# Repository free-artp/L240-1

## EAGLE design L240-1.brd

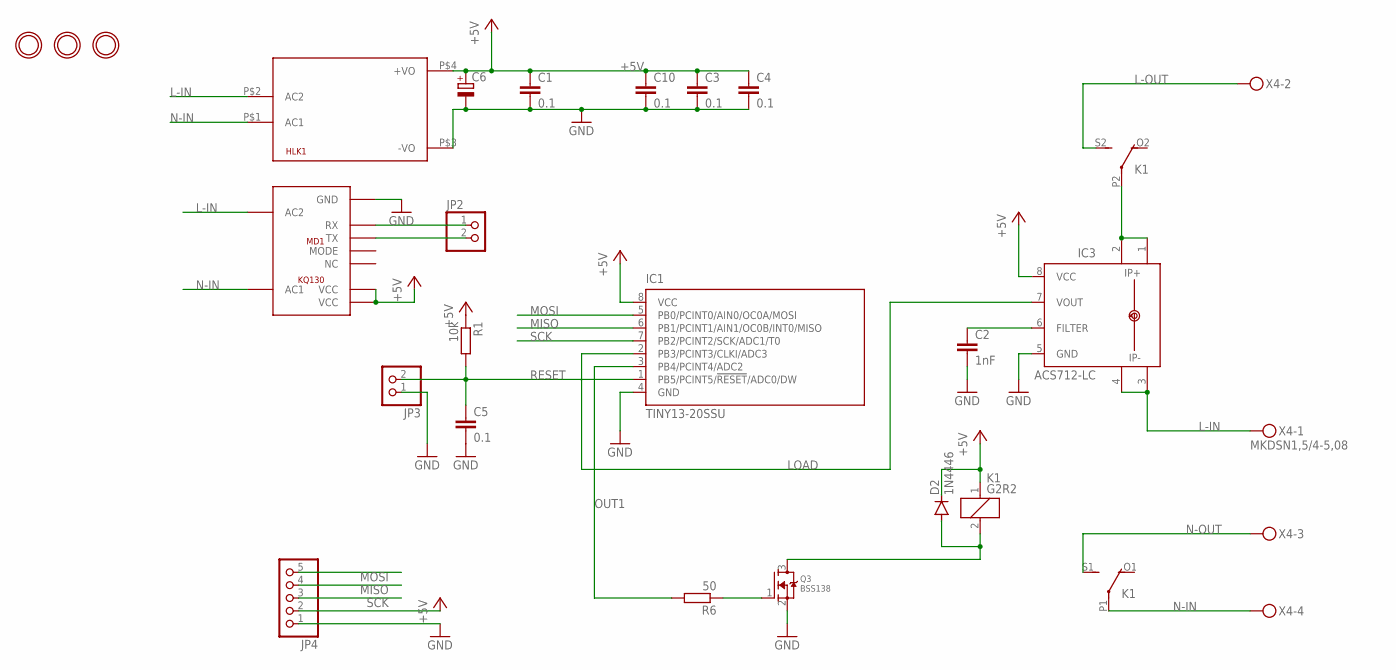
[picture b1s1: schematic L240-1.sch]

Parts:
C1, C3, C4, C5, C10: 0.1; C0805
C2: 1nF; C0805
C6: CPOL-EUE5-5; E5-5
D2: 1N4446; DO35-10
HLK1: HLK-PM013W; HLK-PM01
IC1: TINY13-20SSU; 8S1
IC3: ACS712-LC; SOIC8
JP2, JP3: PINHD-1X2; 1X02
JP4: PINHD-1X5; 1X05
K1: G2R2
MD1: KQ130
Q3: BSS138; SOT23-WIDE
R1: 10k; R0805
R6: 50; R0805
U$1, U$2, U$3: MOUNTINGHOLE3.0THIN; MOUNTINGHOLE_3.0_PLATEDTHIN
X4: MKDSN1,5/4-5,08

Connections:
+5V: C1.1, C3.1, C4.1, C6.+, C10.1, D2.C, HLK1.P$4 (+VO), IC1.8 (VCC), IC3.8 (VCC), JP4.2, K1.1, MD1.VCC@1 (VCC), MD1.VCC@2 (VCC), R1.1
GND: C1.2, C2.2, C3.2, C4.2, C5.2, C6.-, C10.2, HLK1.P$3 (-VO), IC1.4 (GND), IC3.5 (GND), JP3.1, JP4.1, MD1.GND, Q3.2 (S)
L-IN: HLK1.P$2 (AC2), IC3.3 (IP-), IC3.4 (IP-1), MD1.AC2, X4.1
L-OUT: K1.S2 (S), X4.2
LOAD: IC1.2 (PB3/PCINT3/CLKI/ADC3), IC3.7 (VOUT)
MISO: IC1.6 (PB1/PCINT1/AIN1/OC0B/INT0/MISO), JP4.4
MOSI: IC1.5 (PB0/PCINT0/AIN0/OC0A/MOSI), JP4.5
unnamed: JP2.1, MD1.RX
unnamed: IC3.1 (IP+), IC3.2 (IP+1), K1.P2
unnamed: JP2.2, MD1.TX
unnamed: C2.1, IC3.6 (FILTER)
unnamed: Q3.1 (G), R6.1
unnamed: D2.A, K1.2, Q3.3 (D)
N-IN: HLK1.P$1 (AC1), K1.P1, MD1.AC1, X4.4
N-OUT: K1.S1 (S), X4.3
OUT1: IC1.3 (PB4/PCINT4/ADC2), R6.2
RESET: C5.1, IC1.1 (PB5/PCINT5/!RESET!/ADC0/DW), JP3.2, R1.2
SCK: IC1.7 (PB2/PCINT2/SCK/ADC1/T0), JP4.3

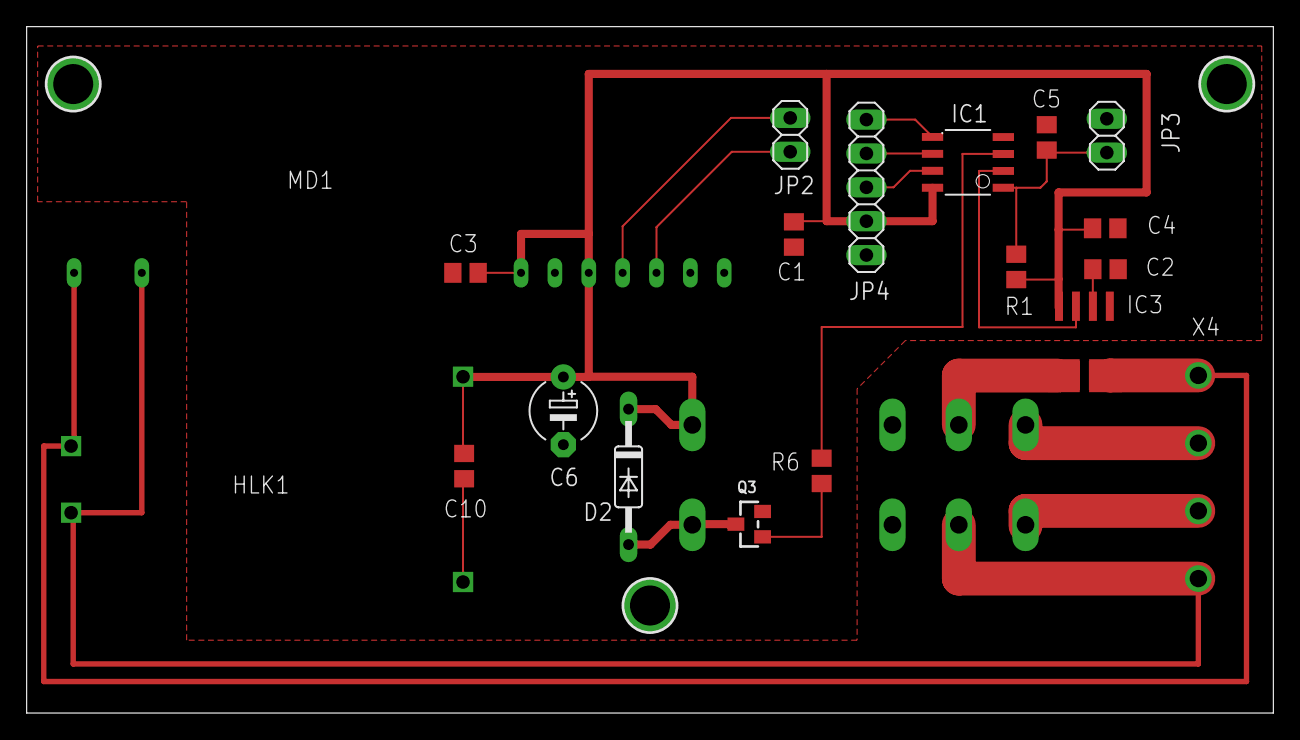
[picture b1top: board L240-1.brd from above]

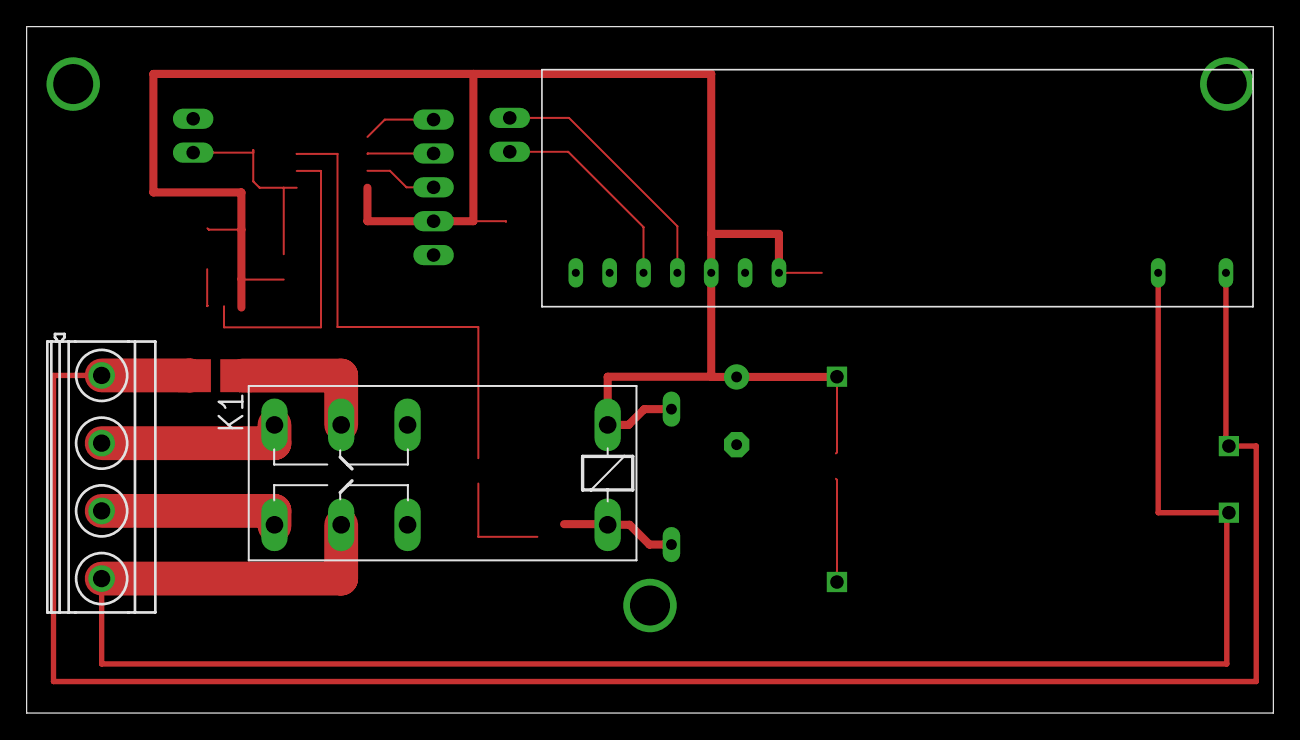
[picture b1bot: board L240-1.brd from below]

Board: 2 copper layers, 93.5 x 51.5 mm, 23 parts (4 on the bottom side), 18 nets.

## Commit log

2019-10-28 initial
2019-10-29 relay
2019-10-31 v0.1
2019-10-31 v0.2
2019-10-31 v0.3
2019-10-31 v0.4
2019-10-31 v0.5
2019-11-01 v1.0
2019-11-01 v1.1
